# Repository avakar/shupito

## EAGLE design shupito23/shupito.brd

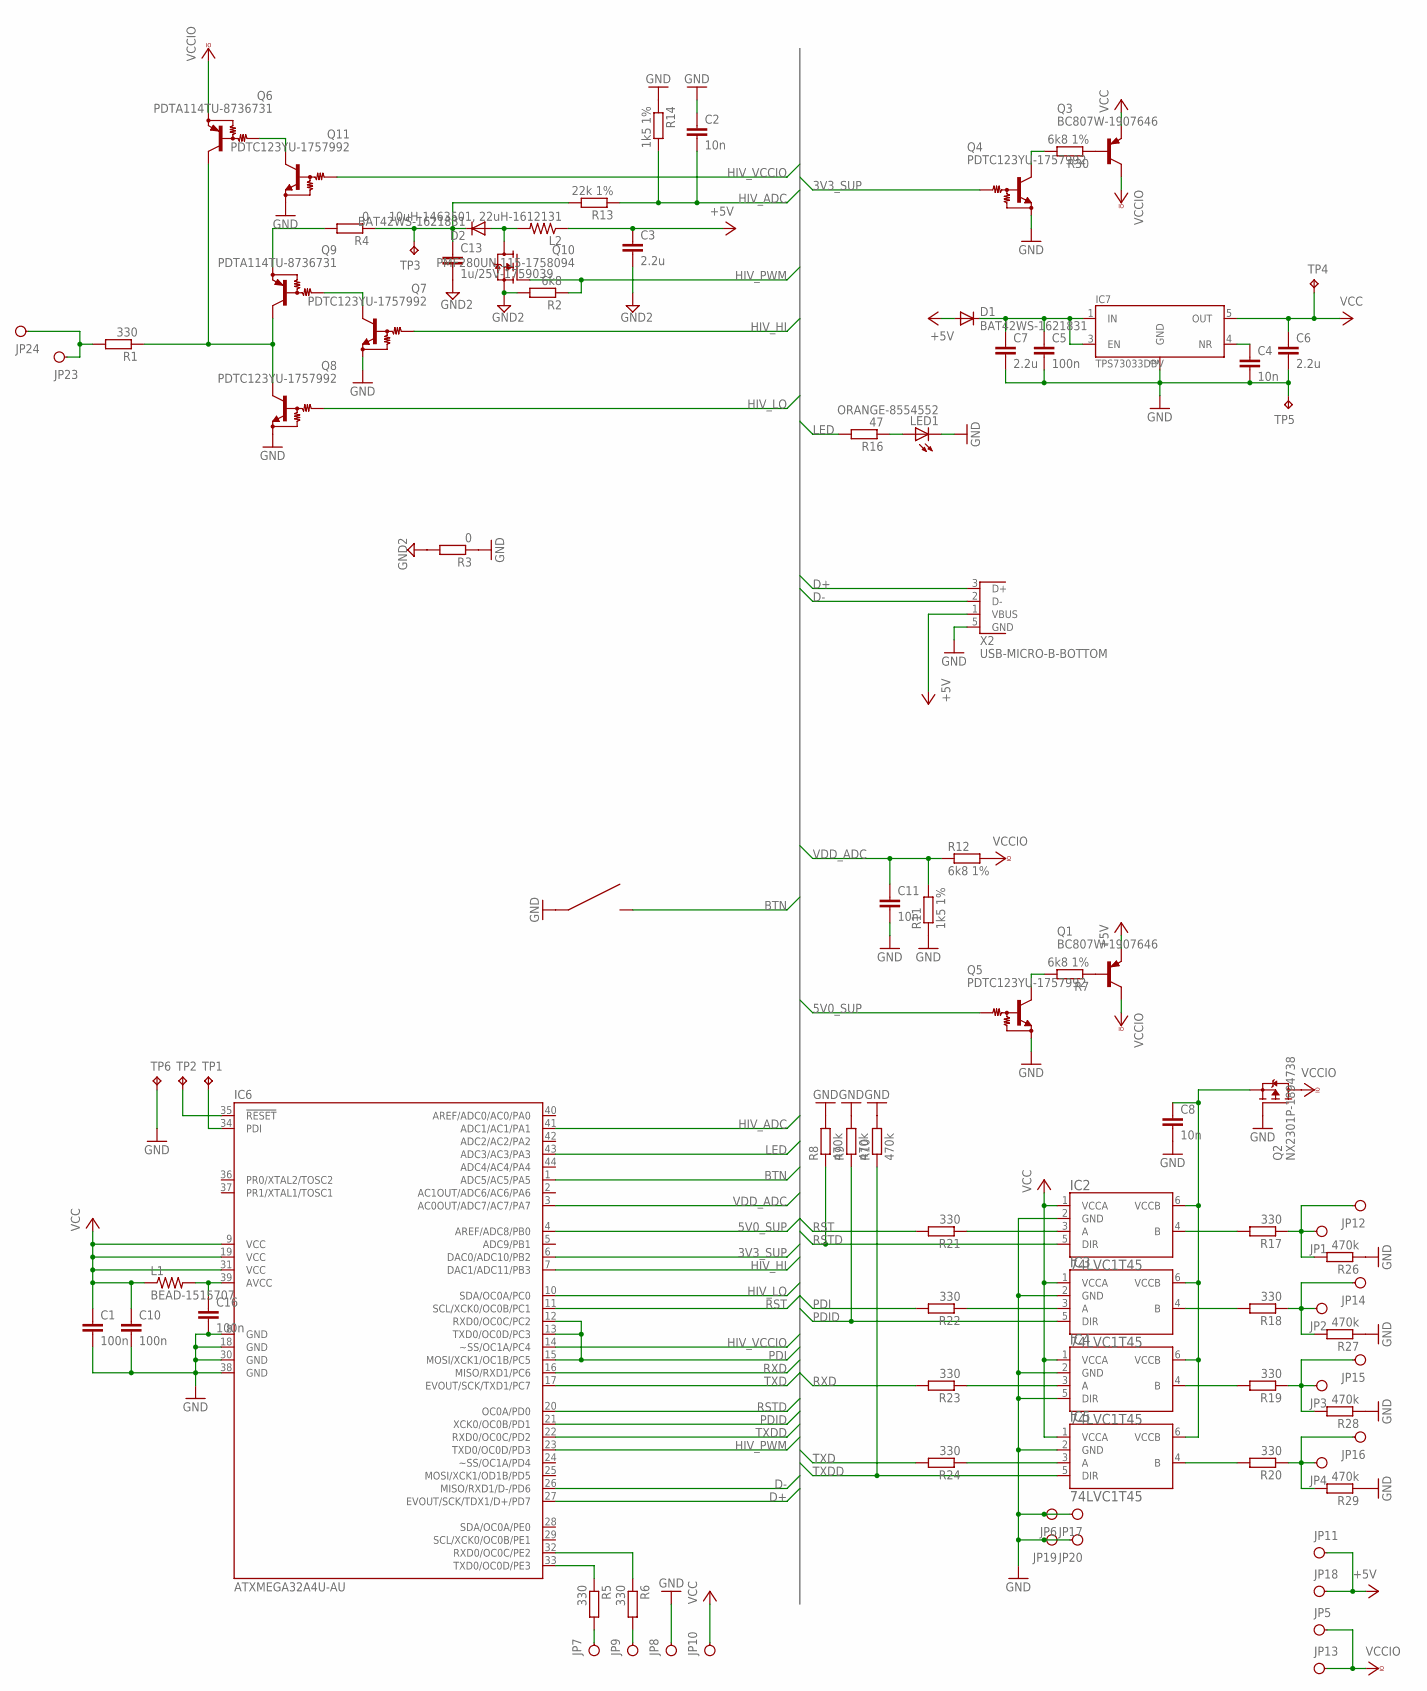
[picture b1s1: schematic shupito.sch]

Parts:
C1, C5, C10, C16: 100n; C0603K
C2, C4, C8, C11: 10n; C0603K
C3, C6, C7: 2.2u; C0603K
C13: 1u/25V-1759039; C0603K
D1, D2: BAT42WS-1621831; SOD323
IC2, IC3, IC4, IC5: 74LVC1T45; SOT236
IC6: ATXMEGA32A4U-AU; TQFP44
IC7: TPS73033DBV; SOT23-DBV
JP1, JP2, JP3, JP4, JP5, JP6, JP7, JP8, JP9, JP10, JP11, JP12, JP13, JP14, JP15, JP16, JP17, JP18, JP19, JP20, JP23, JP24: PINH1X01SMD
L1: BEAD-1515707; R0603
L2: 10uH-1463501, 22uH-1612131; R0805
LED1: ORANGE-8554552; CHIPLED_0603
Q1, Q3: BC807W-1907646; SOT323-BEC
Q2: NX2301P-1894738; SOT23
Q4, Q5, Q7, Q8, Q11: PDTC123YU-1757992; SOT323
Q6, Q9: PDTA114TU-8736731; SOT323
Q10: PMF280UN,115-1758094; SOT323
R1, R5, R6, R17, R18, R19, R20, R21, R22, R23, R24: 330; R0603
R2: 6k8; R0603
R3, R4: 0; R1206
R7, R12, R30: 6k8 1%; R0603
R8, R9, R10, R26, R27, R28, R29: 470k; R0603
R11, R14: 1k5 1%; R0603
R13: 22k 1%; R0603
R16: 47; R0603
S1: KSS241G; KSS-G
TP1, TP2, TP3, TP4, TP5, TP6: TPTP15SQ; TP15SQ
X2: USB-MICRO-B-BOTTOM; USB-MICRO-B-BOTTOM-MOLEX

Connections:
3V3_SUP: IC6.6 (DAC0/ADC10/PB2), Q4.1 (B)
5V0_SUP: IC6.4 (AREF/ADC8/PB0), Q5.1 (B)
+5V: C3.1, D1.A, JP11.1, JP18.1, L2.1, Q1.2 (E), X2.1 (VBUS)
BTN: IC6.1 (ADC5/AC5/PA5), S1.2
D+: IC6.27 (EVOUT/SCK/TDX1/D+/PD7), X2.3 (D+)
D-: IC6.26 (MISO/RXD1/D-/PD6), X2.2 (D-)
GND: C1.2, C2.1, C4.2, C5.2, C6.2, C7.2, C8.2, C10.2, C11.2, C16.2, IC2.2 (GND), IC3.2 (GND), IC4.2 (GND), IC4.5 (DIR), IC5.2 (GND), IC6.8 (GND), IC6.18 (GND), IC6.30 (GND), IC6.38 (GND), IC7.2 (GND), JP6.1, JP8.1, JP17.1, JP19.1, JP20.1, LED1.C, Q2.1 (G), Q4.2 (E), Q5.2 (E), Q7.2 (E), Q8.2 (E), Q11.2 (E), R3.1, R8.2, R9.2, R10.2, R11.1, R14.1, R26.1, R27.1, R28.1, R29.1, S1.1, TP5.TP, TP6.TP, X2.5 (GND)
GND2: C3.2, C13.2, Q10.2 (S), R2.2, R3.2
HIV_ADC: C2.2, IC6.41 (ADC1/AC1/PA1), R13.1, R14.2
HIV_HI: IC6.7 (DAC1/ADC11/PB3), Q7.1 (B)
HIV_LO: IC6.10 (SDA/OC0A/PC0), Q8.1 (B)
HIV_PWM: IC6.23 (TXD0/OC0D/PD3), Q10.1 (G), R2.1
HIV_VCCIO: IC6.14 (~SS/OC1A/PC4), Q11.1 (B)
LED: IC6.43 (ADC3/AC3/PA3), R16.2
unnamed: IC6.33 (TXD0/OC0D/PE3), R5.1
unnamed: IC6.35 (!RESET), TP2.TP
unnamed: IC6.34 (PDI), TP1.TP
unnamed: D2.A, L2.2, Q10.3 (D)
unnamed: IC2.4 (B), R17.2
unnamed: C16.1, IC6.39 (AVCC), L1.2
unnamed: JP2.1, JP14.1, R18.1, R27.2
unnamed: JP23.1, JP24.1, R1.2
unnamed: IC3.4 (B), R18.2
unnamed: Q6.1 (B), Q11.3 (C)
unnamed: Q9.2 (E), R4.2
unnamed: IC6.32 (RXD0/OC0C/PE2), R6.1
unnamed: C5.1, C7.1, D1.C, IC7.1 (IN), IC7.3 (EN)
unnamed: JP7.1, R5.2
unnamed: LED1.A, R16.1
unnamed: Q7.3 (C), Q9.1 (B)
unnamed: C4.1, IC7.4 (NR)
unnamed: JP9.1, R6.2
unnamed: Q1.1 (B), R7.1
unnamed: C13.1, D2.C, R4.1, R13.2, TP3.TP
unnamed: Q5.3 (C), R7.2
unnamed: IC4.4 (B), R19.2
unnamed: Q4.3 (C), R30.2
unnamed: IC5.4 (B), R20.2
unnamed: Q3.1 (B), R30.1
unnamed: C8.1, IC2.6 (VCCB), IC3.6 (VCCB), IC4.6 (VCCB), IC5.6 (VCCB), Q2.2 (S)
unnamed: IC2.3 (A), R21.1
unnamed: IC3.3 (A), R22.1
unnamed: IC4.3 (A), R23.1
unnamed: IC5.3 (A), R24.1
unnamed: JP1.1, JP12.1, R17.1, R26.2
unnamed: JP3.1, JP15.1, R19.1, R28.2
unnamed: JP4.1, JP16.1, R20.1, R29.2
unnamed: Q6.3 (C), Q8.3 (C), Q9.3 (C), R1.1
PDI: IC6.12 (RXD0/OC0C/PC2), IC6.13 (TXD0/OC0D/PC3), IC6.15 (MOSI/XCK1/OC1B/PC5), R22.2
PDID: IC3.5 (DIR), IC6.21 (XCK0/OC0B/PD1), R9.1
RST: IC6.11 (SCL/XCK0/OC0B/PC1), R21.2
RSTD: IC2.5 (DIR), IC6.20 (OC0A/PD0), R8.1
RXD: IC6.16 (MISO/RXD1/PC6), R23.2
TXD: IC6.17 (EVOUT/SCK/TXD1/PC7), R24.2
TXDD: IC5.5 (DIR), IC6.22 (RXD0/OC0C/PD2), R10.1
VCC: C1.1, C6.1, C10.1, IC2.1 (VCCA), IC3.1 (VCCA), IC4.1 (VCCA), IC5.1 (VCCA), IC6.9 (VCC), IC6.19 (VCC), IC6.31 (VCC), IC7.5 (OUT), JP10.1, L1.1, Q3.2 (E), TP4.TP
VCCIO: JP5.1, JP13.1, Q1.3 (C), Q2.3 (D), Q3.3 (C), Q6.2 (E), R12.2
VDD_ADC: C11.1, IC6.3 (AC0OUT/ADC7/AC7/PA7), R11.2, R12.1

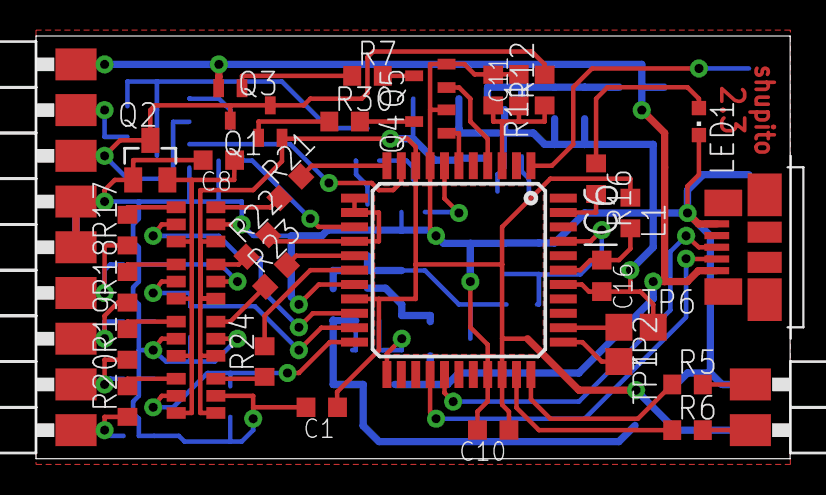
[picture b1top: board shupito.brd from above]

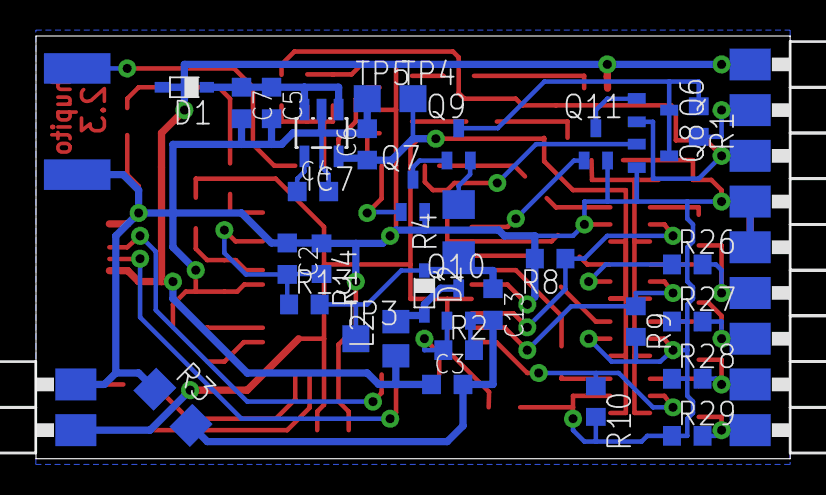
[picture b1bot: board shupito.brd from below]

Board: 2 copper layers, 41.9 x 23.5 mm, 92 parts (45 on the bottom side), 58 nets.

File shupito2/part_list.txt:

Partlist

Exported from shupito.sch at 12/9/2011 4:29:12 PM

EAGLE Version 5.11.0 Copyright (c) 1988-2010 CadSoft

Part     Value             Device              Package      Library        Sheet

C1       100n              C-EUC0603           C0603        rcl            1
C9       100n              C-EUC0603           C0603        rcl            1
C10      100n              C-EUC0603           C0603        rcl            1
C12      100n              C-EUC0603           C0603        rcl            1
C5       100n              C-EUC0603           C0603        rcl            1
C16      100n              C-EUC0603           C0603        rcl            1

C8       10n               C-EUC0603           C0603        rcl            1
C11      10n               C-EUC0603           C0603        rcl            1
C13      10n               C-EUC0603           C0603        rcl            1
C4       10n               C-EUC0603           C0603        rcl            1

C2       18p               C-EUC0603           C0603        rcl            1
C3       18p               C-EUC0603           C0603        rcl            1

R1       330               R-EU_R0603          R0603        rcl            1
R2       330               R-EU_R0603          R0603        rcl            1
R3       330               R-EU_R0603          R0603        rcl            1
R4       330               R-EU_R0603          R0603        rcl            1
R17      330               R-EU_R0603          R0603        rcl            1
R18      330               R-EU_R0603          R0603        rcl            1
R19      330               R-EU_R0603          R0603        rcl            1
R20      330               R-EU_R0603          R0603        rcl            1
R21      330               R-EU_R0603          R0603        rcl            1
R22      330               R-EU_R0603          R0603        rcl            1
R23      330               R-EU_R0603          R0603        rcl            1
R24      330               R-EU_R0603          R0603        rcl            1

R5       22                R-EU_R0603          R0603        rcl            1
R6       22                R-EU_R0603          R0603        rcl            1

R8       470k              R-EU_R0603          R0603        rcl            1
R9       470k              R-EU_R0603          R0603        rcl            1
R25      470k              R-EU_R0603          R0603        rcl            1
R26      470k              R-EU_R0603          R0603        rcl            1
R27      470k              R-EU_R0603          R0603        rcl            1
R28      470k              R-EU_R0603          R0603        rcl            1
R29      470k              R-EU_R0603          R0603        rcl            1
R10      470k              R-EU_R0603          R0603        rcl            1


R7       6k8               R-EU_R0603          R0603        rcl            1
R12      6k8               R-EU_R0603          R0603        rcl            1
R14      6k8               R-EU_R0603          R0603        rcl            1
R30      6k8               R-EU_R0603          R0603        rcl            1

R11      1k5               R-EU_R0603          R0603        rcl            1
R15      1k5               R-EU_R0603          R0603        rcl            1

C6       2.2u              C-EUC1206           C1206        rcl            1
C7       4.7u              C-EUC1206           C1206        rcl            1

D1       BAT42WS-1621831   DIODE-SOD323        SOD323       diode          1
D3       BAT42WS-1621831   DIODE-SOD323        SOD323       diode          1

D2       PMEG2005-1757760  DIODE-SOD323        SOD323       diode          1
D4       PMEG2005-1757760  DIODE-SOD323        SOD323       diode          1

IC6      ATMEGA8U2         ATMEGA8U2           TQFP32-08    atmega_u2      1

C14      10u-1759434       C-EUC1206           C1206        rcl            1
C15      68u-1672624       CPOL-EUC/6032-28R   C/6032-28R   rcl            1
R16      47                R-EU_R0603          R0603        rcl            1


IC1      AVR_XMEGA_A4_44A  AVR_XMEGA_A4_44A    TQFP44       xmega          1
IC2      74LVC1T45         74LVC1T45DBV        SOT236       74lvc1t45      1
IC3      74LVC1T45         74LVC1T45DBV        SOT236       74lvc1t45      1
IC4      74LVC1T45         74LVC1T45DBV        SOT236       74lvc1t45      1
IC5      74LVC1T45         74LVC1T45DBV        SOT236       74lvc1t45      1
IC7      TPS73033DBV       TPS73033DBV         SOT23-DBV    tps73033       1
IC8      NCP1400A          NCP1400A            SOT23-DBV    ncp1400a       1
L1       BEAD-1515707      R-US_R0603          R0603        rcl            1
L2       22u-1782802       L                   1515         inductors      1
Q1       BC807W-1907646    BC807W              SOT323-BEC   transistor-pnp 1
Q3       BC807W-1907646    BC807W              SOT323-BEC   transistor-pnp 1
Q2       NX2301P-1894738   P-MOSFET-SOT23-GSD  SOT23        transistors    1
Q4       PDTC123YU-1757992 NPN-BIAS-SOT323-BEC SOT323       transistors    1
Q5       PDTC123YU-1757992 NPN-BIAS-SOT323-BEC SOT323       transistors    1

X1                         USB-MB-S            USB-MB-S     con-usb-3      1
X2       ABMM2-8MHz        XTAL6X3.6_LARGE     6X3.6_LARGE  xtal           1
LED1     ORANGE-8554552    LEDCHIPLED_0603     CHIPLED_0603 led            1

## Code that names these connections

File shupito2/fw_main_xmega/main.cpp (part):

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
AVRLIB_DEFINE_XMEGA_PIN(pin_led,     PORTA, 2);

AVRLIB_DEFINE_XMEGA_PIN(pin_pdid, PORTD, 1);
AVRLIB_DEFINE_XMEGA_PIN(pin_rstd, PORTD, 0);
AVRLIB_DEFINE_XMEGA_PIN(pin_rst,  PORTC, 1);

AVRLIB_DEFINE_XMEGA_PIN(pin_pdi,  PORTC, 3);
AVRLIB_DEFINE_XMEGA_PIN(pin_xck,  PORTC, 5);

AVRLIB_DEFINE_XMEGA_PIN(pin_rxd,  PORTC, 6);
AVRLIB_DEFINE_XMEGA_PIN(pin_txd,  PORTC, 7);
AVRLIB_DEFINE_XMEGA_PIN(pin_txdd, PORTD, 2);

AVRLIB_DEFINE_XMEGA_PIN(pin_usb_rtr_n, PORTD, 3);
AVRLIB_DEFINE_XMEGA_PIN(pin_usb_cts_n, PORTD, 4);
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AVRLIB_DEFINE_XMEGA_PIN(pin_bt_rx, PORTE, 2);
AVRLIB_DEFINE_XMEGA_PIN(pin_bt_tx, PORTE, 3);

typedef pin_buffer_with_oe<pin_txd, pin_txdd> pin_buf_txd;
typedef pin_buffer_with_oe<pin_rst, pin_rstd> pin_buf_rst;
typedef pin_buffer_with_oe<pin_pdi, pin_pdid> pin_buf_pdi;
typedef pin_buffer_with_oe<pin_xck, pin_pdid> pin_buf_xck;
typedef pin_rxd pin_buf_rxd;

typedef avrlib::hwflow_usart<avrlib::usart_xd1, 64, 64, avrlib::intr_med, pin_usb_rtr_n, pin_usb_cts_n> com_inner_t;
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
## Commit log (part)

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2011-03-02 initial import
2011-03-05 Finished routing. Ready for etching.
2011-03-05 Added tag v1.0 for changeset 3d282d9d8dc9
2011-03-12 Added the firmware project with a sketch of the PDI interface driver.
2011-03-12 Added avrlib dependency.
2011-03-12 Added .hgignore.
2011-04-15 Added support for PDI flash memory programming.
2011-04-15 Directory reorganization.
2011-04-15 Added a client software for shupito (forked from avricsp).
2011-04-17 Reading, erasing and programming fuses now works for pdi. icsp is broken.
2011-04-17 Writing flash memory now works.
2011-04-17 Fixed device descriptions for atxmegaa4 devices.
2011-04-25 Factored the PDI-related functionality and command handling out of the main file.
    The main loop now merely dispatches commands (other than command 0) to a handler.
    There is currently only one handler, but more can be added (this is a preparation
    for the readdition of the classical SPI programmer). It will later be possible to
    switch between handlers dynamically through command 0.
2011-04-25 Updated .hgignore.
2011-04-25 Added the 'fuses' memory definition to the chipdefs of all 'avr' chips.
    The memory section is added automatically if it is missing from the definition
    string. The memory section is always four bytes long. For now, all xmega chips
    (which have different size of the fuse memory) have the section defined
    explicitely.
2011-04-25 Added support for the classic AVR SPI programming.
    The SPI programmer is currently selected as the default
    and cannot be changed. The PDI programming capability
    is therefore temporarily disabled.
    The bootseq check is now performed outside the command parsing.
    Otherwise, attempts to flash a program containing the bootload sequence
    would reset the programmer.
2011-07-03 Started v2.0 rework -- xmega and level translators.
2011-07-04 usb chip, reg, ext_sup
2011-07-04 started routing
2011-07-05 routing, phase 1
2011-07-06 some more routing
2011-07-06 some more routing, added support for pinhead receptacle for bth instead of pinheads
2011-07-06 Added voltage measurement, removed a few capacitors.
2011-07-06 added diode, 0402->0603
2011-07-06 4.7u A->1206
2011-07-12 Fuses can now be programmed via SPI ICSP programming.
2011-07-23 Fixed the pagesize of atmega8u2 in the client.
2011-07-23 An early, non-functional sketch of usb chip firmware.
2011-07-23 Added the project file for the USB firmware package.
2011-07-24 USB<->UART translation now basically works.
2011-07-24 Added the libusb0-based driver.
2011-07-24 Merged scripts that generate USB descriptors for usb_fw into a single file.
2011-07-26 Added support for GET_STATUS request, some stalling on errors.
2011-07-26 CDC ACM now works in both Linux and Windows.
2011-07-31 Fixed shupito v1 (m162) firmware so that the slave xmega chip can be stopped and started repeatedly.
2011-08-07 Added firmware for shupito_v2. Untested.
2011-08-07 Fixed the output stage (DIR is powered by VCCA), rerouted.
2011-08-11 The USB chip's oscillator now drives xmega's clock input.
2011-08-11 Connected XCK between the chips (allowing synchronous USART for faster communication).
2011-08-11 Added components for a switched supply. Needs placement and routing.
2011-08-12 Switched supply placement and routing.
2011-08-14 Finished power supply design, replaced 5VOUT transistor with a bipolar one.
2011-08-14 Repositioned the switched and LDO supplies. Added LED.
2011-08-14 Increased the width of power lines.
2011-08-14 Slight rearrangement.
2011-08-14 Repositioning.
2011-08-14 Fixed up values of some parts.
2011-08-16 Fixed values of adc resistor dividers.
2011-08-16 Added protective resistors; final touches.
2011-08-16 Some more DRC settings.
2011-08-29 Added tag v2.0 for changeset 84e12908941b
2011-09-11 Fixed bootrst fuse settings for atxmega a4 devices.
2011-09-17 Basic piping from xmega to usb chip. No wrap in xmega->pc direction.
2011-09-18 Added transmit pipe wrapping.
2011-09-20 New yb descriptor protocol, spi/pdi handlers, sketch of VDD measurement.
2011-09-22 Added VDD measurement and control, fixed the device desc,.
2011-09-22 vdd_drive is now ordered <hiz>, 5V.
2011-09-24 A bit of refactoring.
2011-09-25 xmega now provides clock for the inner USART communication.
2011-09-25 Added a sync-usart bootloader for USB chip.
2011-09-25 Removed debug print statements from USB chip output.
2011-09-25 Updated avrlib.
2011-09-25 Fixed usb firmware to work with 8MHz crystal.
2011-09-25 Added the 'app' pipe.
2011-09-26 Fixed pin assignments and polarity. app pipe now works correctly.
2011-09-28 USB test mode.
2011-09-28 USB chip no longer cancels its own IN packets.
2011-09-28 OUT packets are now forwarded without blocking the IN direction.
2011-10-03 PDI works, except that disabling PDI will not unreset the chip.
2011-10-04 PDI now works.
2011-10-05 SPI programming now works. ADC slowed down to allow the SH cap to charge.
2011-10-07 Changed the tunnel protocol a bit.
2011-10-08 app pipe now gets automatically disabled when spi is enabled.
2011-10-08 VCCIO measurement and safeguards.
2011-10-08 PDI is now correctly cleared when an error occurs.
2011-10-09 Updated to a newer avrlib (optimized async_usart).
2011-10-09 Modified interrupt priorities slightly.
2011-10-09 Slowed down the main clock (no need for such a high precision).
2011-10-15 board: hw flow control, prep for 3v3 ext sup, output pull-downs.
2011-10-15 Prepared for flow-controlled inner comm.
2011-10-15 Default RTR/CTS settings.
2011-10-16 hwflow sketch
2011-10-16 3v3 ext sup, adc filter
2011-10-28 Slowed JTAG programming.
2011-10-28 Moved some files around.
2011-10-28 Re-added shupito0 firmware.
2011-10-28 shupito1 firmware now compiles again.
2011-10-28 Updated shupito1 to use yb descriptors.
2011-10-28 Rename.
2011-10-29 Consolidated parts, created partlist.
2011-10-29 A few final touches.
2011-10-29 Added CLOCK command to the jtag handler.
2011-11-06 Shupito JTAG now responds to FREQUENCY command.
2011-11-17 Final revision.
2011-11-20 USB no longer bootloads when connected via the USB.
2011-11-20 Fixed read memory in SPI mode.
2011-11-26 Fixed read memory command for xmega.
2011-11-26 Emergency supply shutdown is now done even during long reads.
2011-11-26 Added eeprom read/write for spi.
2011-11-27 Programming frequency can now be set.
2011-11-29 Fixed the delay between reset and prog enable sequence in spi.
2011-12-03 Decreased the VCCIO emergency shutdown voltage to 4.4V.
2011-12-03 Fixed a few PDI time constants.
2011-12-03 Added a 100us wait when switching from RX to TX (PDI requires at least one idle bit).
2011-12-04 Color codes.
2011-12-10 Fixed handling of chips larger than 0x8000.
2011-12-11 The main chip now provides clock for the USB chip (at 16MHz with DFLL from 32kHz RC osc).
2011-12-11 3.3V output support, reverted USB chip to 8MHz (can't run at 16MHz at this voltage).
2011-12-11 Updated the inf file for shupito CDC.
2011-12-16 Added VUSB measurement, switched reg control.
2011-12-16 A bunch of hex files.
2011-12-29 Fixed the USB driver.
2012-01-08 Added support for Texas Instrument's CC25xx chips.
2012-01-08 Fixed USB descriptors (product name/manufacturer).
2012-01-08 Added cc25xx write optimization.
2012-03-24 Some more routing.
2012-03-24 Added a button, placement and routing.
2012-03-25 Routed.
2012-03-25 Done.
2012-03-26 Added a protection diode for the 3.3v ldo.
2012-03-30 Added generic SPI communication.
2012-04-01 Added hardware flow control to shupito 2.2
2012-04-04 Added usb stream test.
2012-04-04 Fixed internal flow control.
2012-04-04 Removed usb test mode.
2012-04-06 Fixed flow control (hw can't be used on 8u2 due to the lack of hw control on the xmega side).
2012-04-07 Main loop will now keep running even after the client disconnects.
2012-04-07 Upgraded to AVR Studio 5, added version info to the device's yb descriptor.
2012-04-07 Time offset is now stored in minutes in yb desc.
2012-04-07 Removed stale builds.
2012-06-24 prog_uint8_t is no longer supported, changed to uint8_t.
2012-06-24 Things seem to work with -O2 instead of -Os. More investigation is needed.
2012-06-24 Shupito no longer creates /dev/ttyACM0 devices.
2012-06-24 Upgraded usb_fw to AVR studio 5.
2012-06-30 Shupito now has serial numbers.
2012-06-30 Added alternate ways to enter bootloader for the usb chip.
2012-07-29 avricsp now respects fuse read size and offset.
2012-09-18 Added GND and VCC to AUX connector.
2012-09-19 Added protective resistors.
2012-09-30 Updated partlist.
2012-10-23 Increased drill size to 0.5mm.
2012-11-05 Added a part name.
2012-11-10 Removed old usb_fw.
2012-11-10 Added DFU bootloader patched to use PA5.
2012-11-17 Bootloader patch attempt backup.
2012-11-17 shupito2->shupito23 in preparation of branch merge
2012-12-14 Proper USB S/N is now sent.
2012-12-17 vccio and tunnel sketch for shupito23
2012-12-19 shupito23: pdi support
2012-12-19 Removed a generated file.
2012-12-19 shupito23: spi
2012-12-19 Fixed a warning.
2012-12-19 Proper tunnel support.
2012-12-20 Marked tunnel interface as supporting extended control codes.
2012-12-20 A bit of power and noise reduction.
2012-12-20 Basic support for high voltage generation.
2012-12-21 shupito23: Selected better transistors for the rst pin.
2012-12-21 shupito23: RST pin now support hiv output.
2012-12-21 shupito23: fixed up yb descriptor.
2012-12-21 shupito23: refactoring, removed some debug prints.
2012-12-21 Added averaging filter for vccio measurements.
2012-12-21 shupito23: the control endpoints now have smaller buffers
2012-12-22 Added support for starting the bootloader.
2012-12-22 shupito23: hardware button
2012-12-22 Led will now blink on tunnel connect or on host trigger.
2012-12-22 shupito23: Made the long blink longer.
2013-01-13 Added a test command to transmit a full packet.
2013-01-13 shupito23: added another thunner through the bth connector.
2013-01-25 Added front cover layer to shupito23
2013-01-25 Some more front design.
2013-01-25 Some more front cover design
2013-01-25 Front design finalized.
2013-01-27 Added a test protocol for shupito23
2013-01-27 shupito23: updated the .debug interface.
2013-01-27 shupito23: fixed hiv constants.
2013-01-27 shupito23: PDI interface fixes, added debug pins.
2013-01-27 shupito23: updated front design
2013-01-28 shupito23: tunnel writes now go through DMA
2013-01-31 shupito23: fixed baudrate table.
2013-01-31 shupito23: DMA-based tunnel transfers.
2013-02-02 shupito23: fixed settings of tunnel baudrate.
2013-02-02 shupito32: tunnel rx now goes through an 8-way buffer.
2013-02-03 shupito23: added stack usage measurement.
2013-02-03 shupito23: C fixes
2013-02-03 shupito23: tunnel now goes through 05.83 endpoints in preparation for double-buffering.
2013-02-06 shupito23: added USB double-buffering for tunnel.
2013-02-12 shupito23: support for parity and data/stop bit settings for tunnels.
2013-03-09 shupito23: the device name is now stored in eeprom and can be changed
2013-03-10 Updated shupito22 fw to compile after changes to common.
2013-03-11 shupito23: the tunnel no longer interferes with spi
2013-03-15 shupito23: generic SPI communication support
2013-03-23 shupito23: added JTAG support
2013-03-24 shupito23: refactoring in preparation for DMA-based JTAG pattern generation
2013-03-24 shupito23: implemented continuous clock, DMA-based JTAG
2013-03-24 shupito23: added TRST command support
2013-03-24 shupito23: JTAG support refactoring
2013-03-26 shupito23: updated Farnell OC for 2.2uF
2013-03-27 shupito23: fixed up DMA channel priorities
2013-03-27 shupito23: HIV pin handling for JTAG
2013-03-27 shupito22: made compilable
2013-03-27 shupito22: fixed old JTAG support
2013-06-01 shupito23: jtag no longer drops the last bit of a shift
2013-06-16 shupito23: added PWM generator
2013-08-27 shupito23: a .dfu file is now created.
2014-02-16 Something about yb DFU. Not sure what.
2014-02-16 shupito23: increased nvm reset timeout to account for 64ms reset hold
2014-05-11 shupito23: new front design
2014-05-11 avrlib is now pulled from bitbucket
2014-07-27 shupito23: added an echoing usart mode
